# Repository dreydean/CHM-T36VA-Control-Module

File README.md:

View this project on [CADLAB.io](https://cadlab.io/project/2389). 

# CHM-T36VA-Control-Module
This is the control module to the CHM-T36VA pick and place machine. 

This is a work in progress. If anyone is able to contribute to this design please fork this repo! Hopefully this will give the OpenPNP community an opportunity to integrate into the CHM-T36VA. Feel free to contact me with any questions or suggestions!

You can eaily view this board or schematic on www.CADLAB.io

also you can view the Bill of Material here at this link.

BOM = https://octopart.com/bom-tool/2MmSibn2

As the project evolves I will make sure these stay up to date.

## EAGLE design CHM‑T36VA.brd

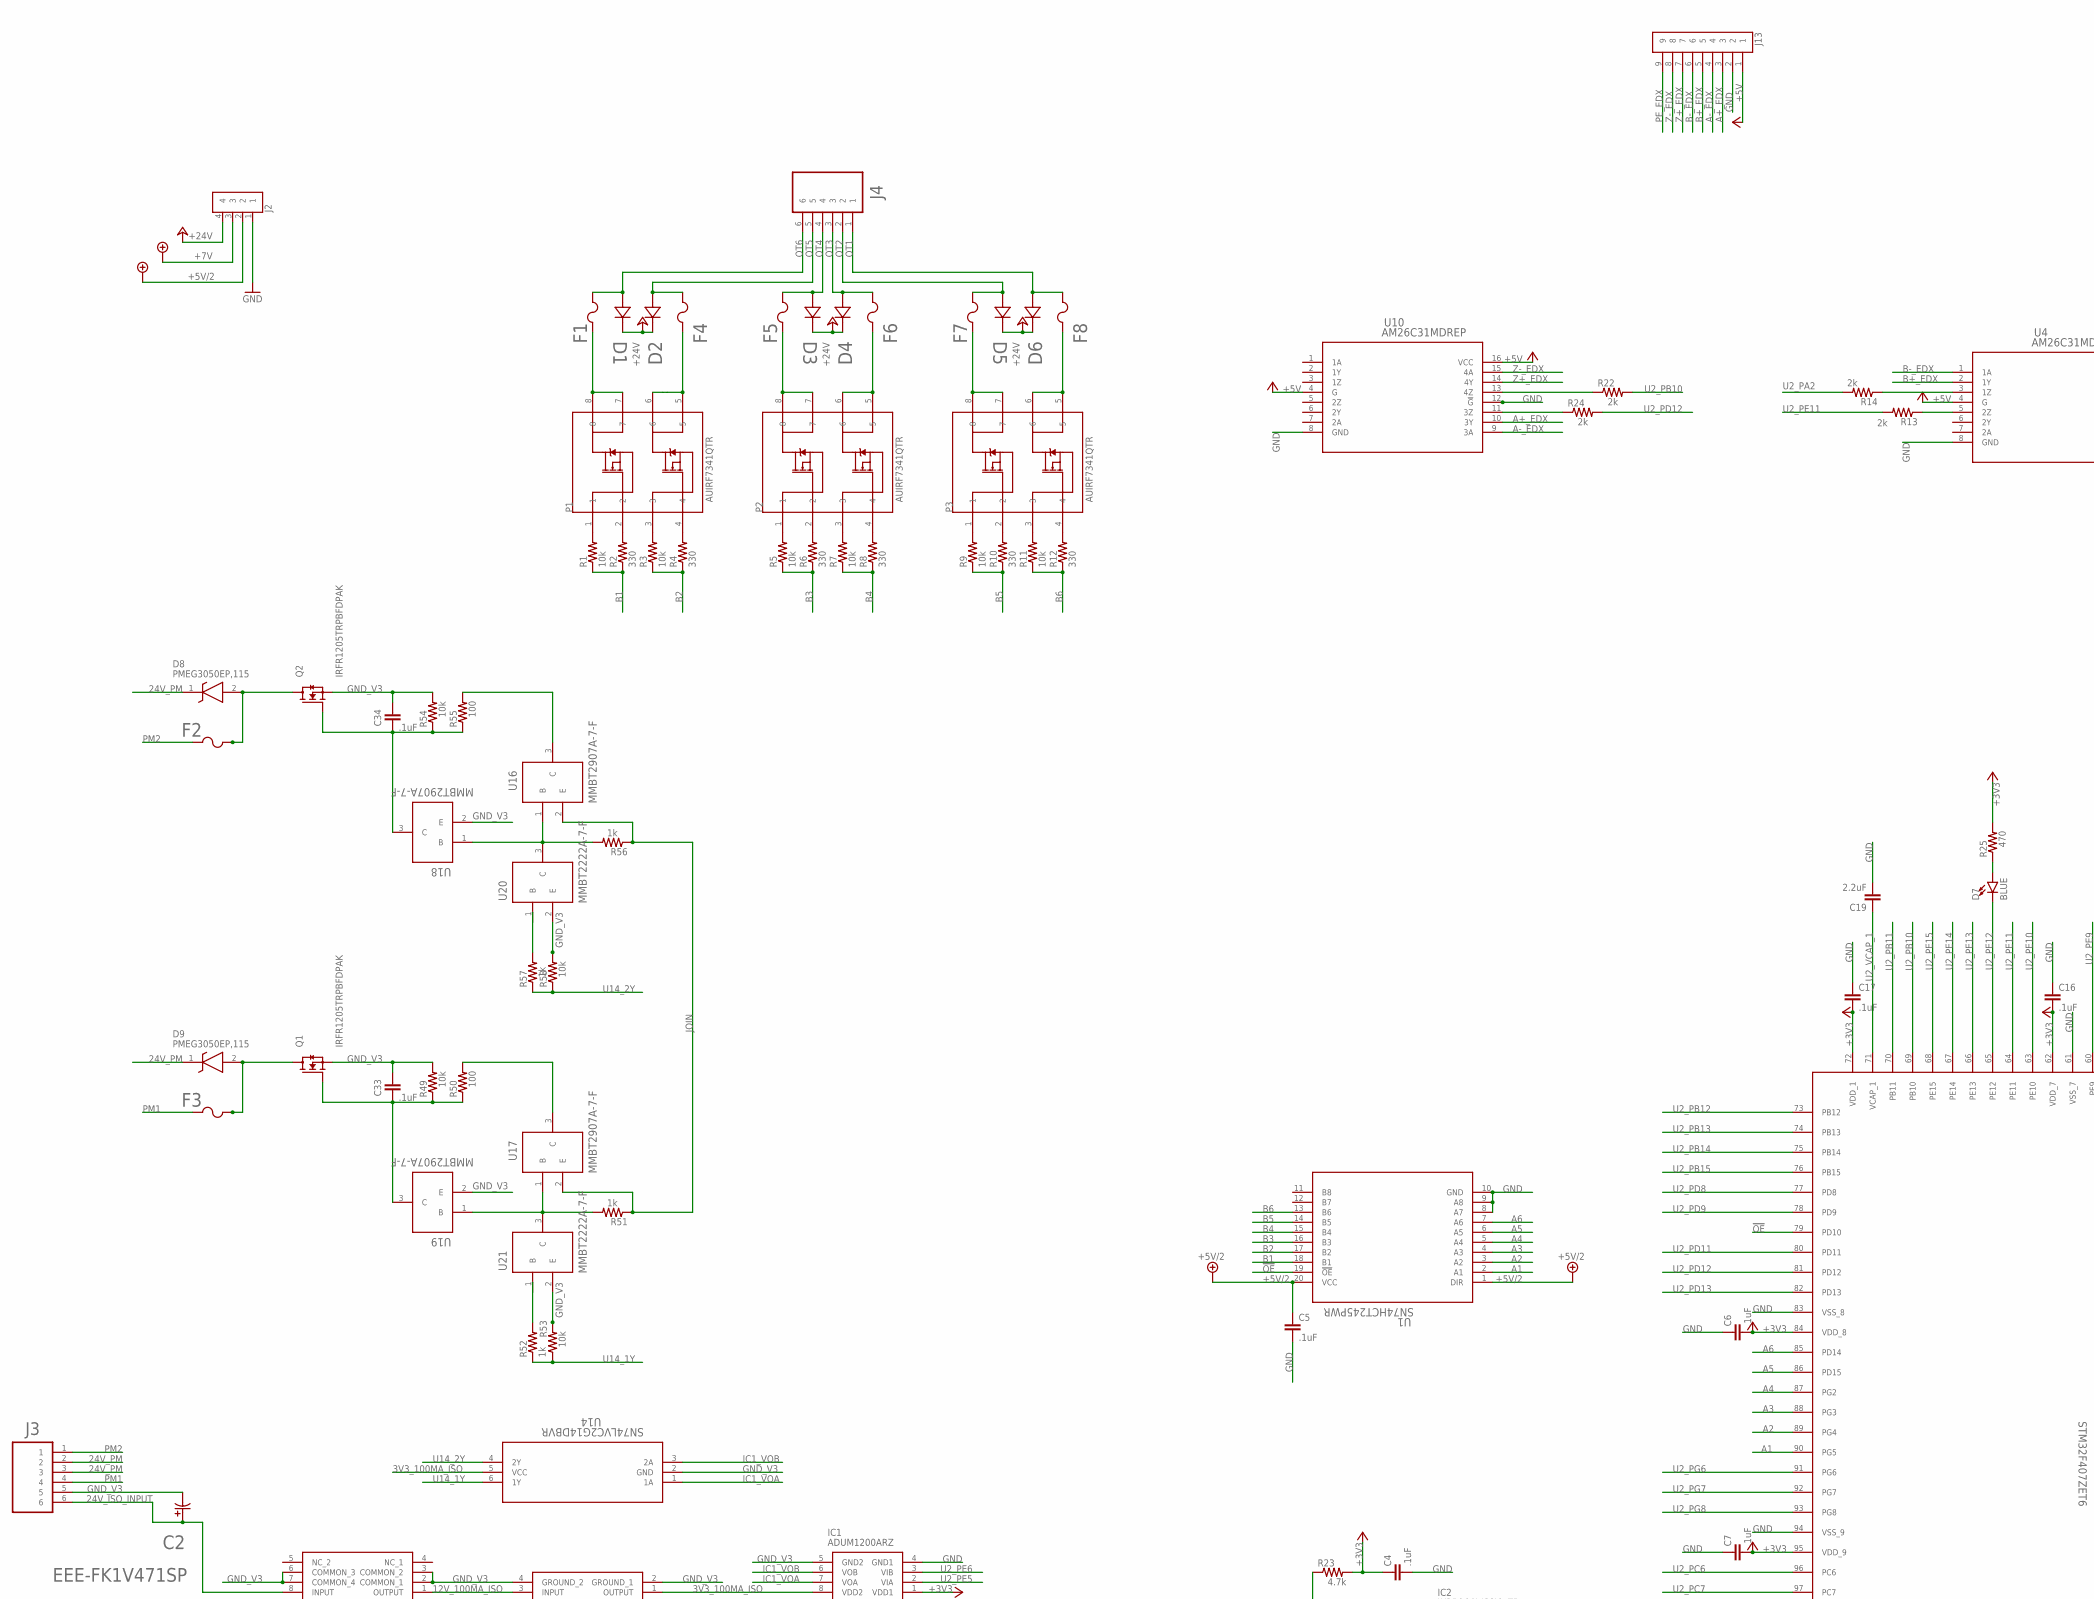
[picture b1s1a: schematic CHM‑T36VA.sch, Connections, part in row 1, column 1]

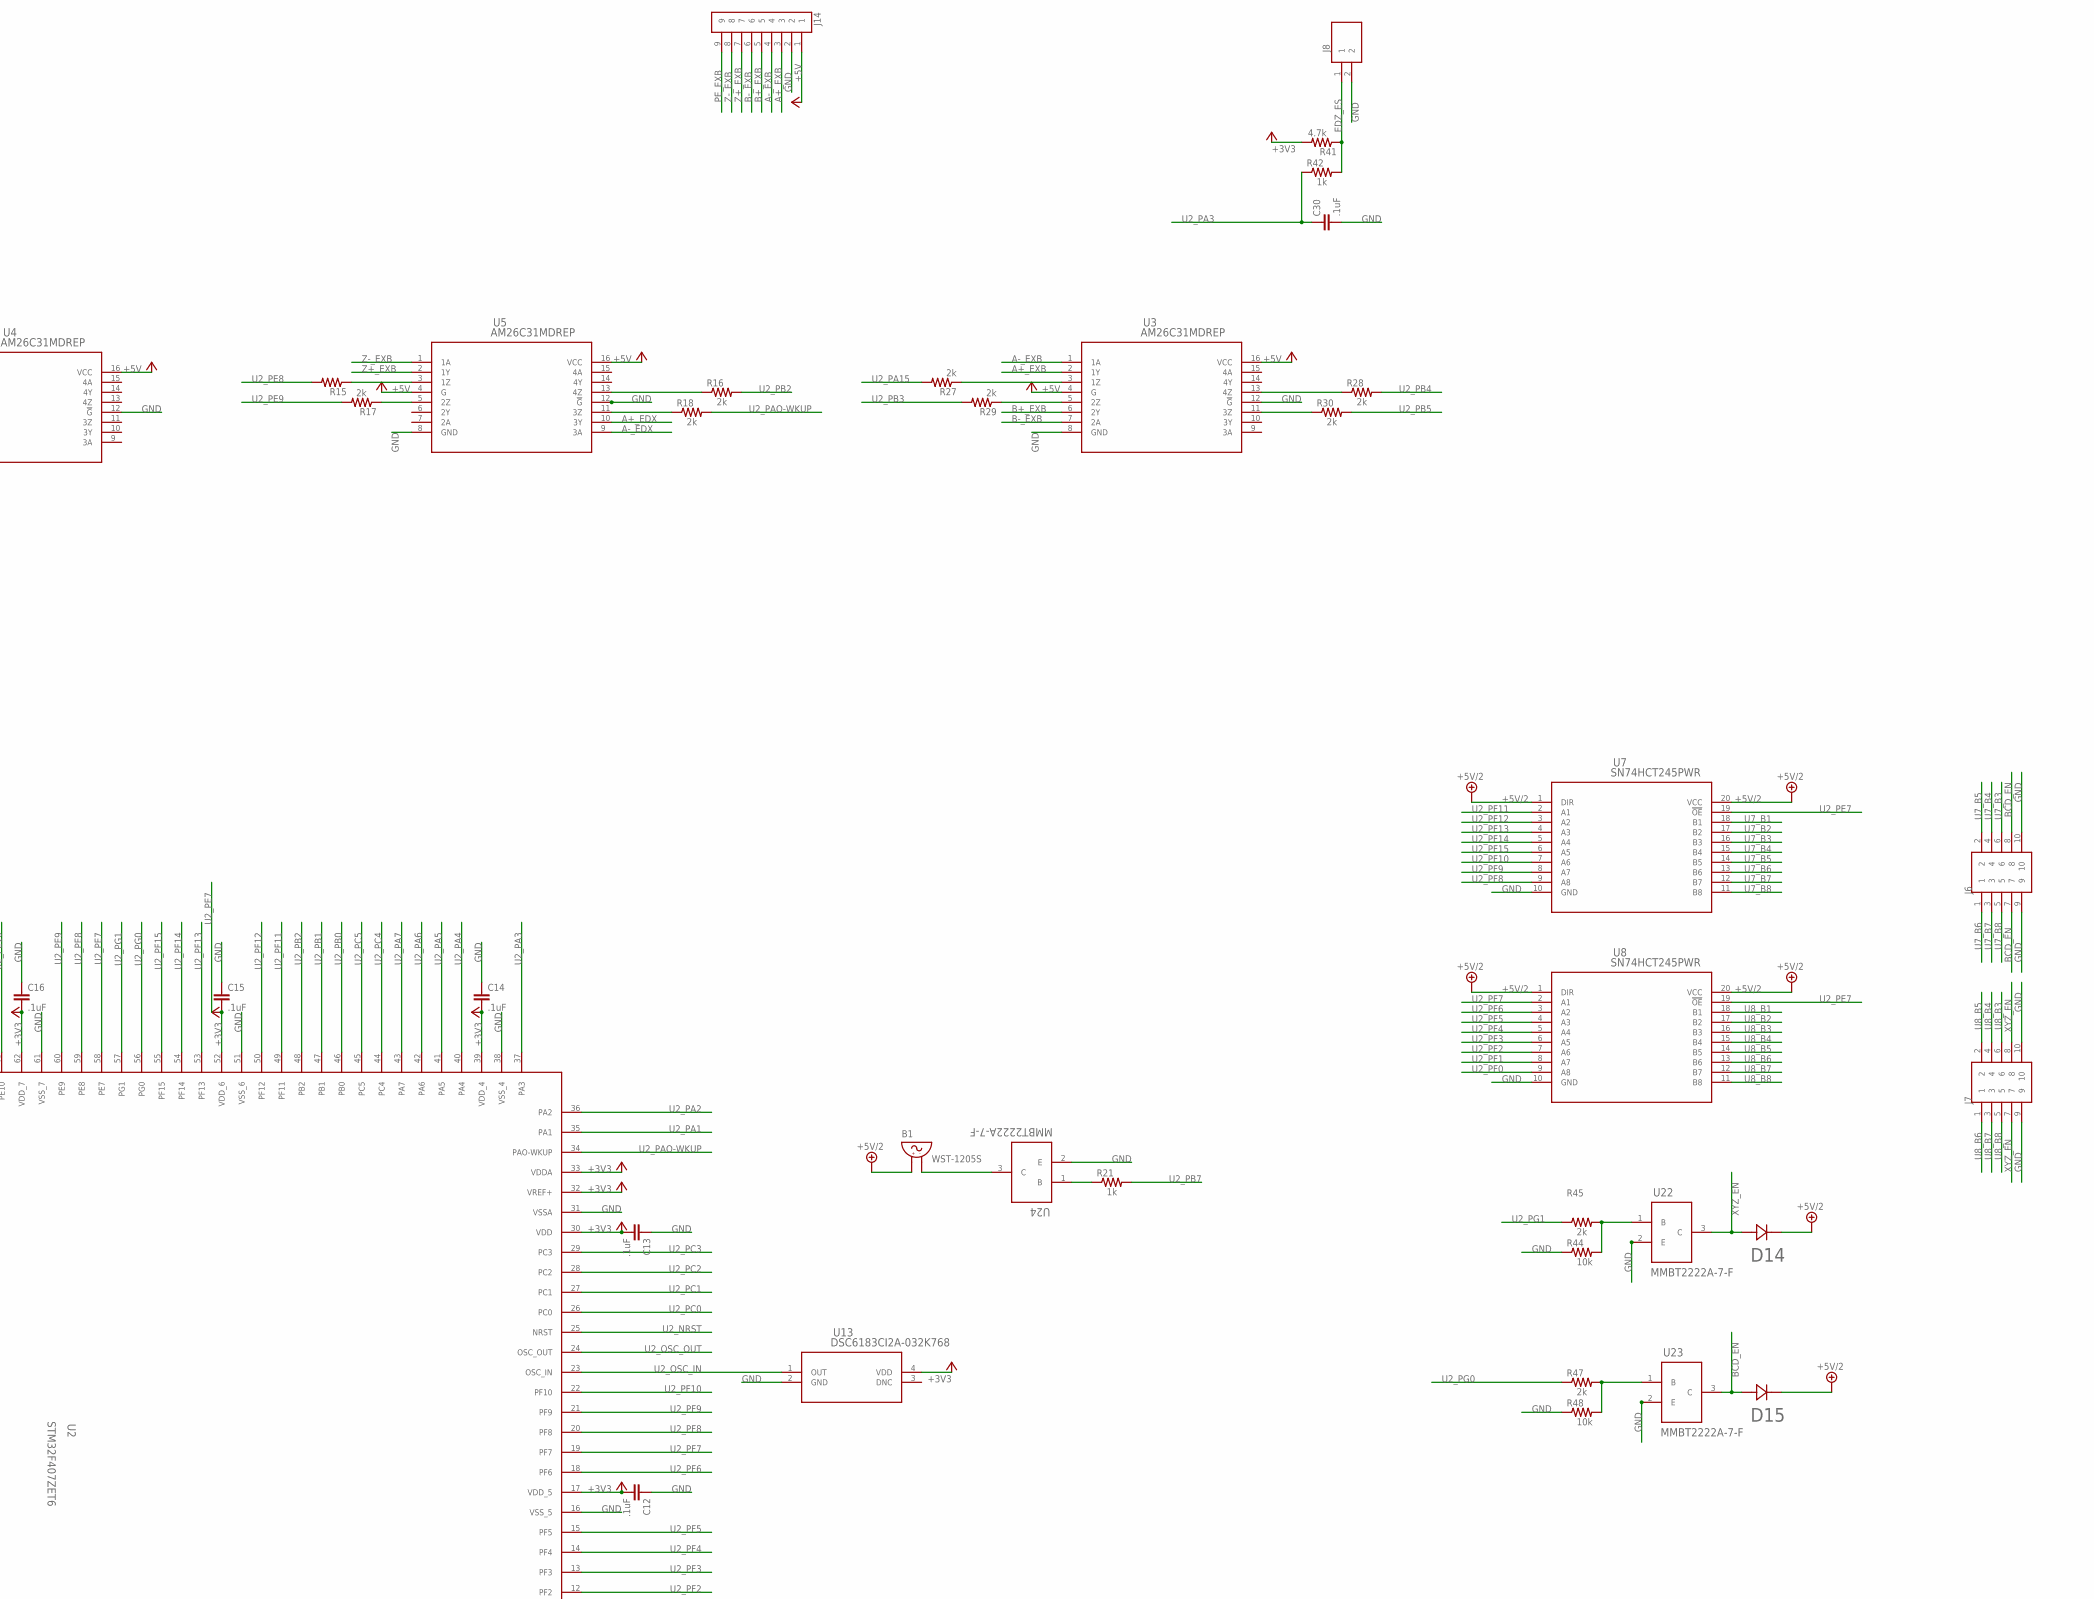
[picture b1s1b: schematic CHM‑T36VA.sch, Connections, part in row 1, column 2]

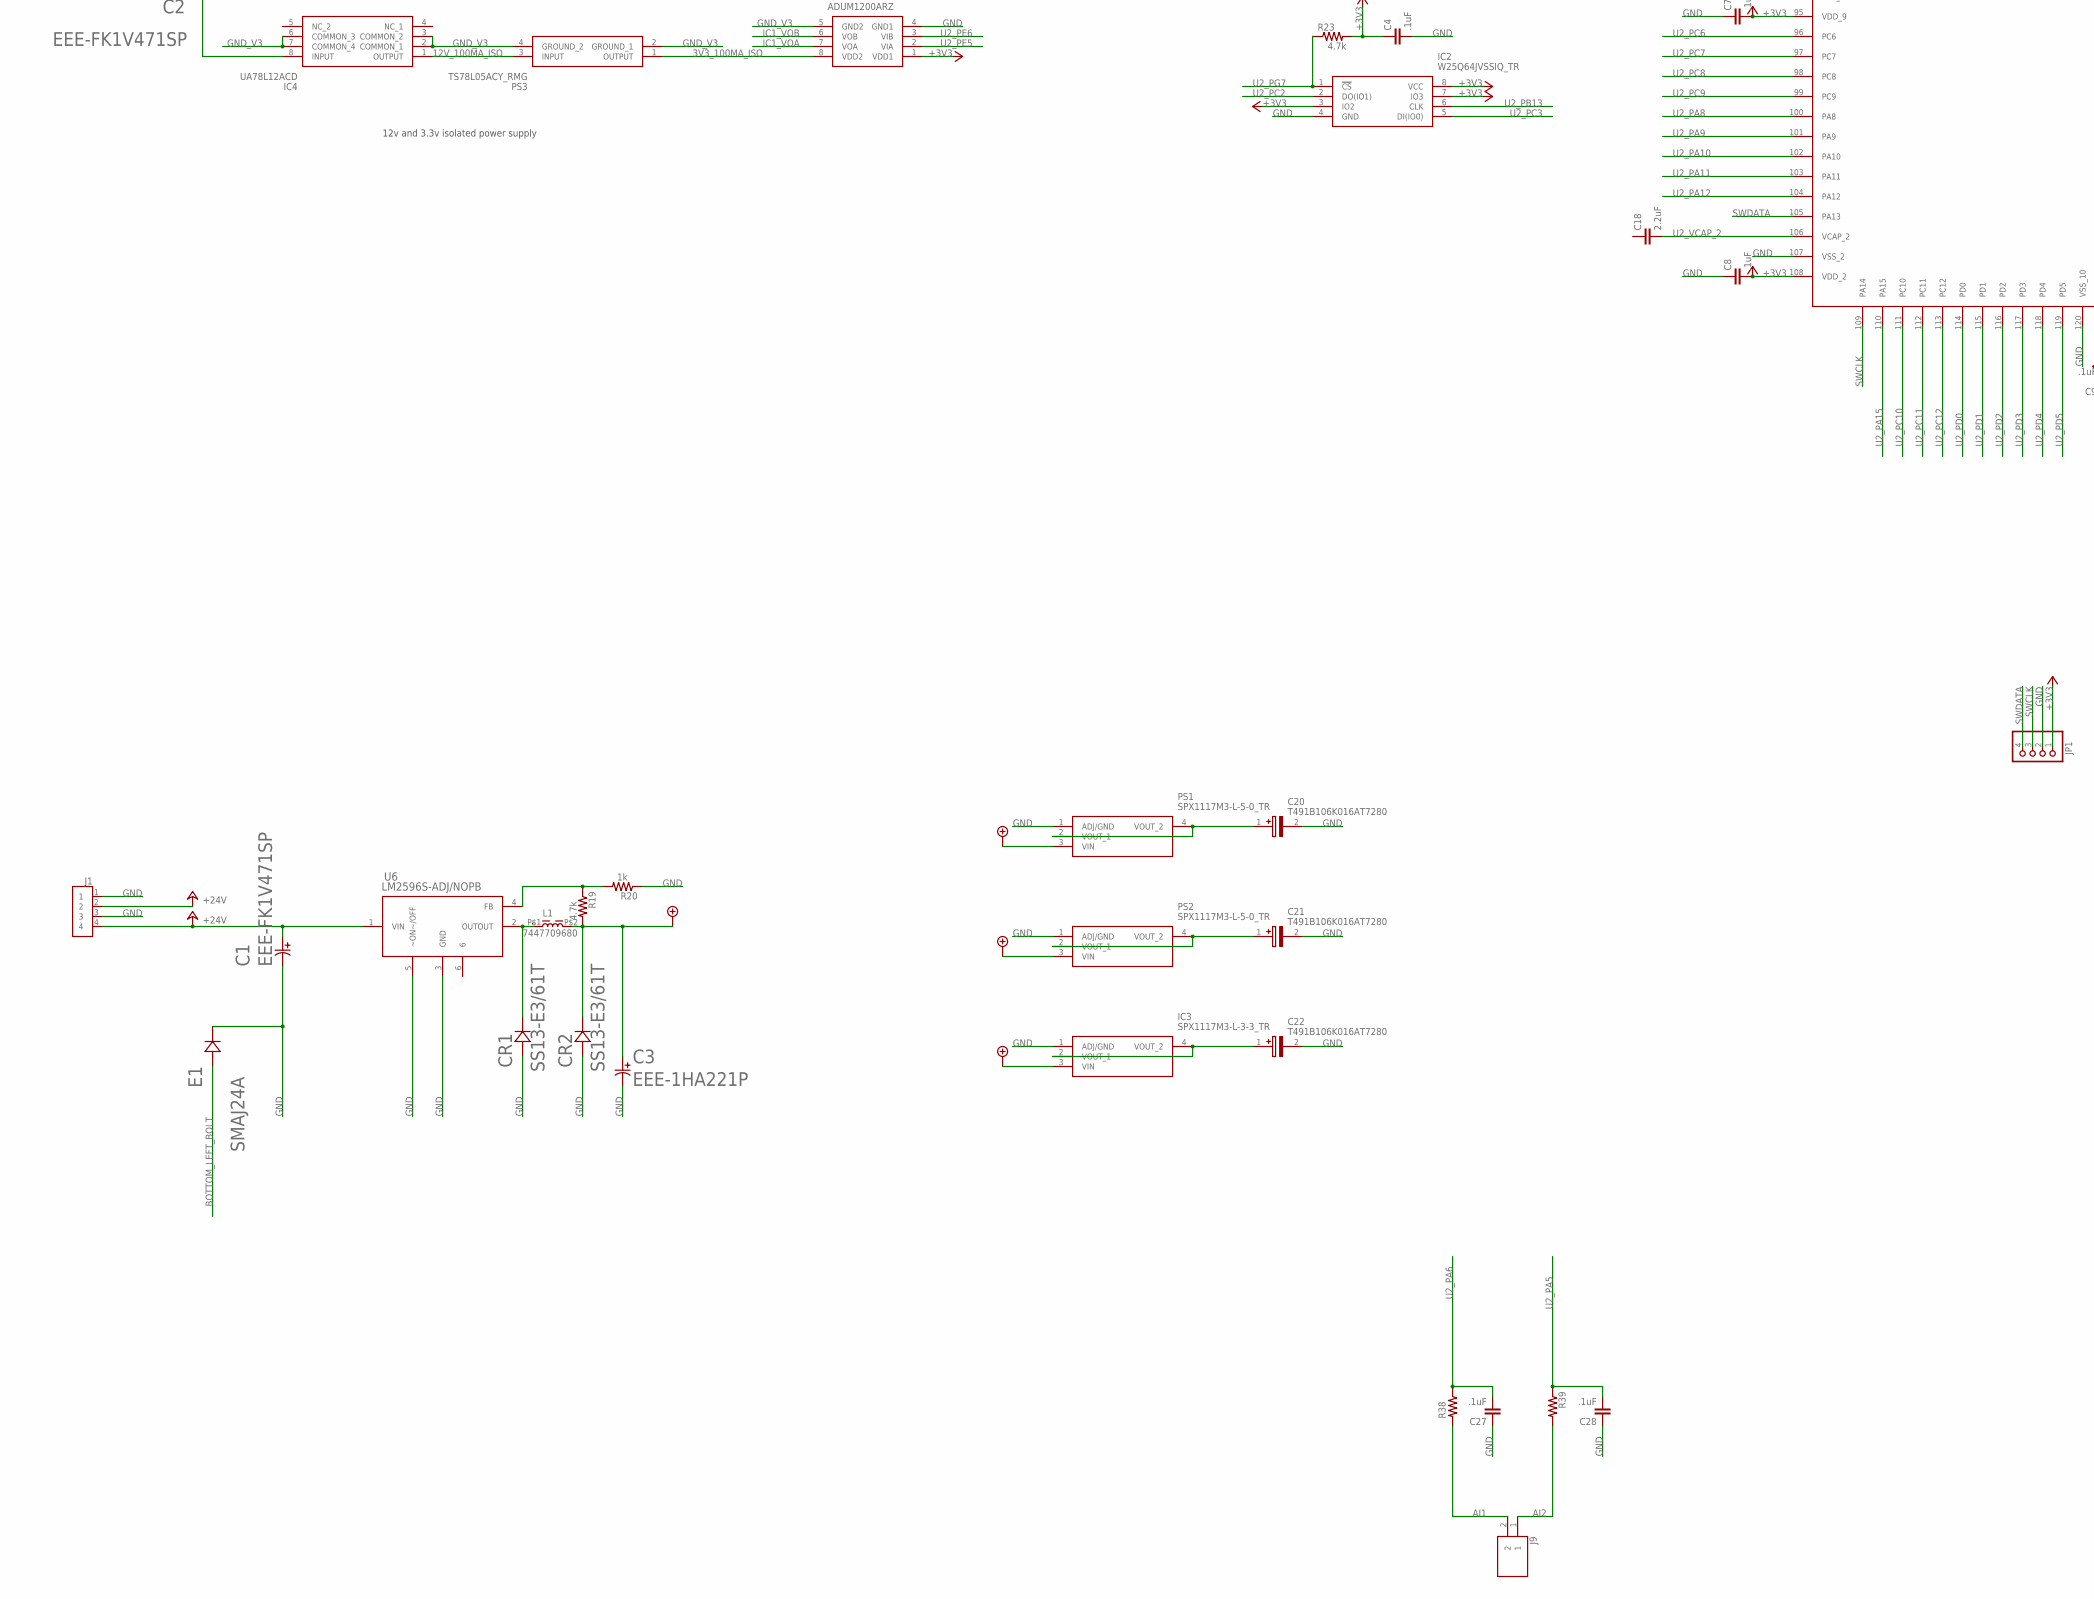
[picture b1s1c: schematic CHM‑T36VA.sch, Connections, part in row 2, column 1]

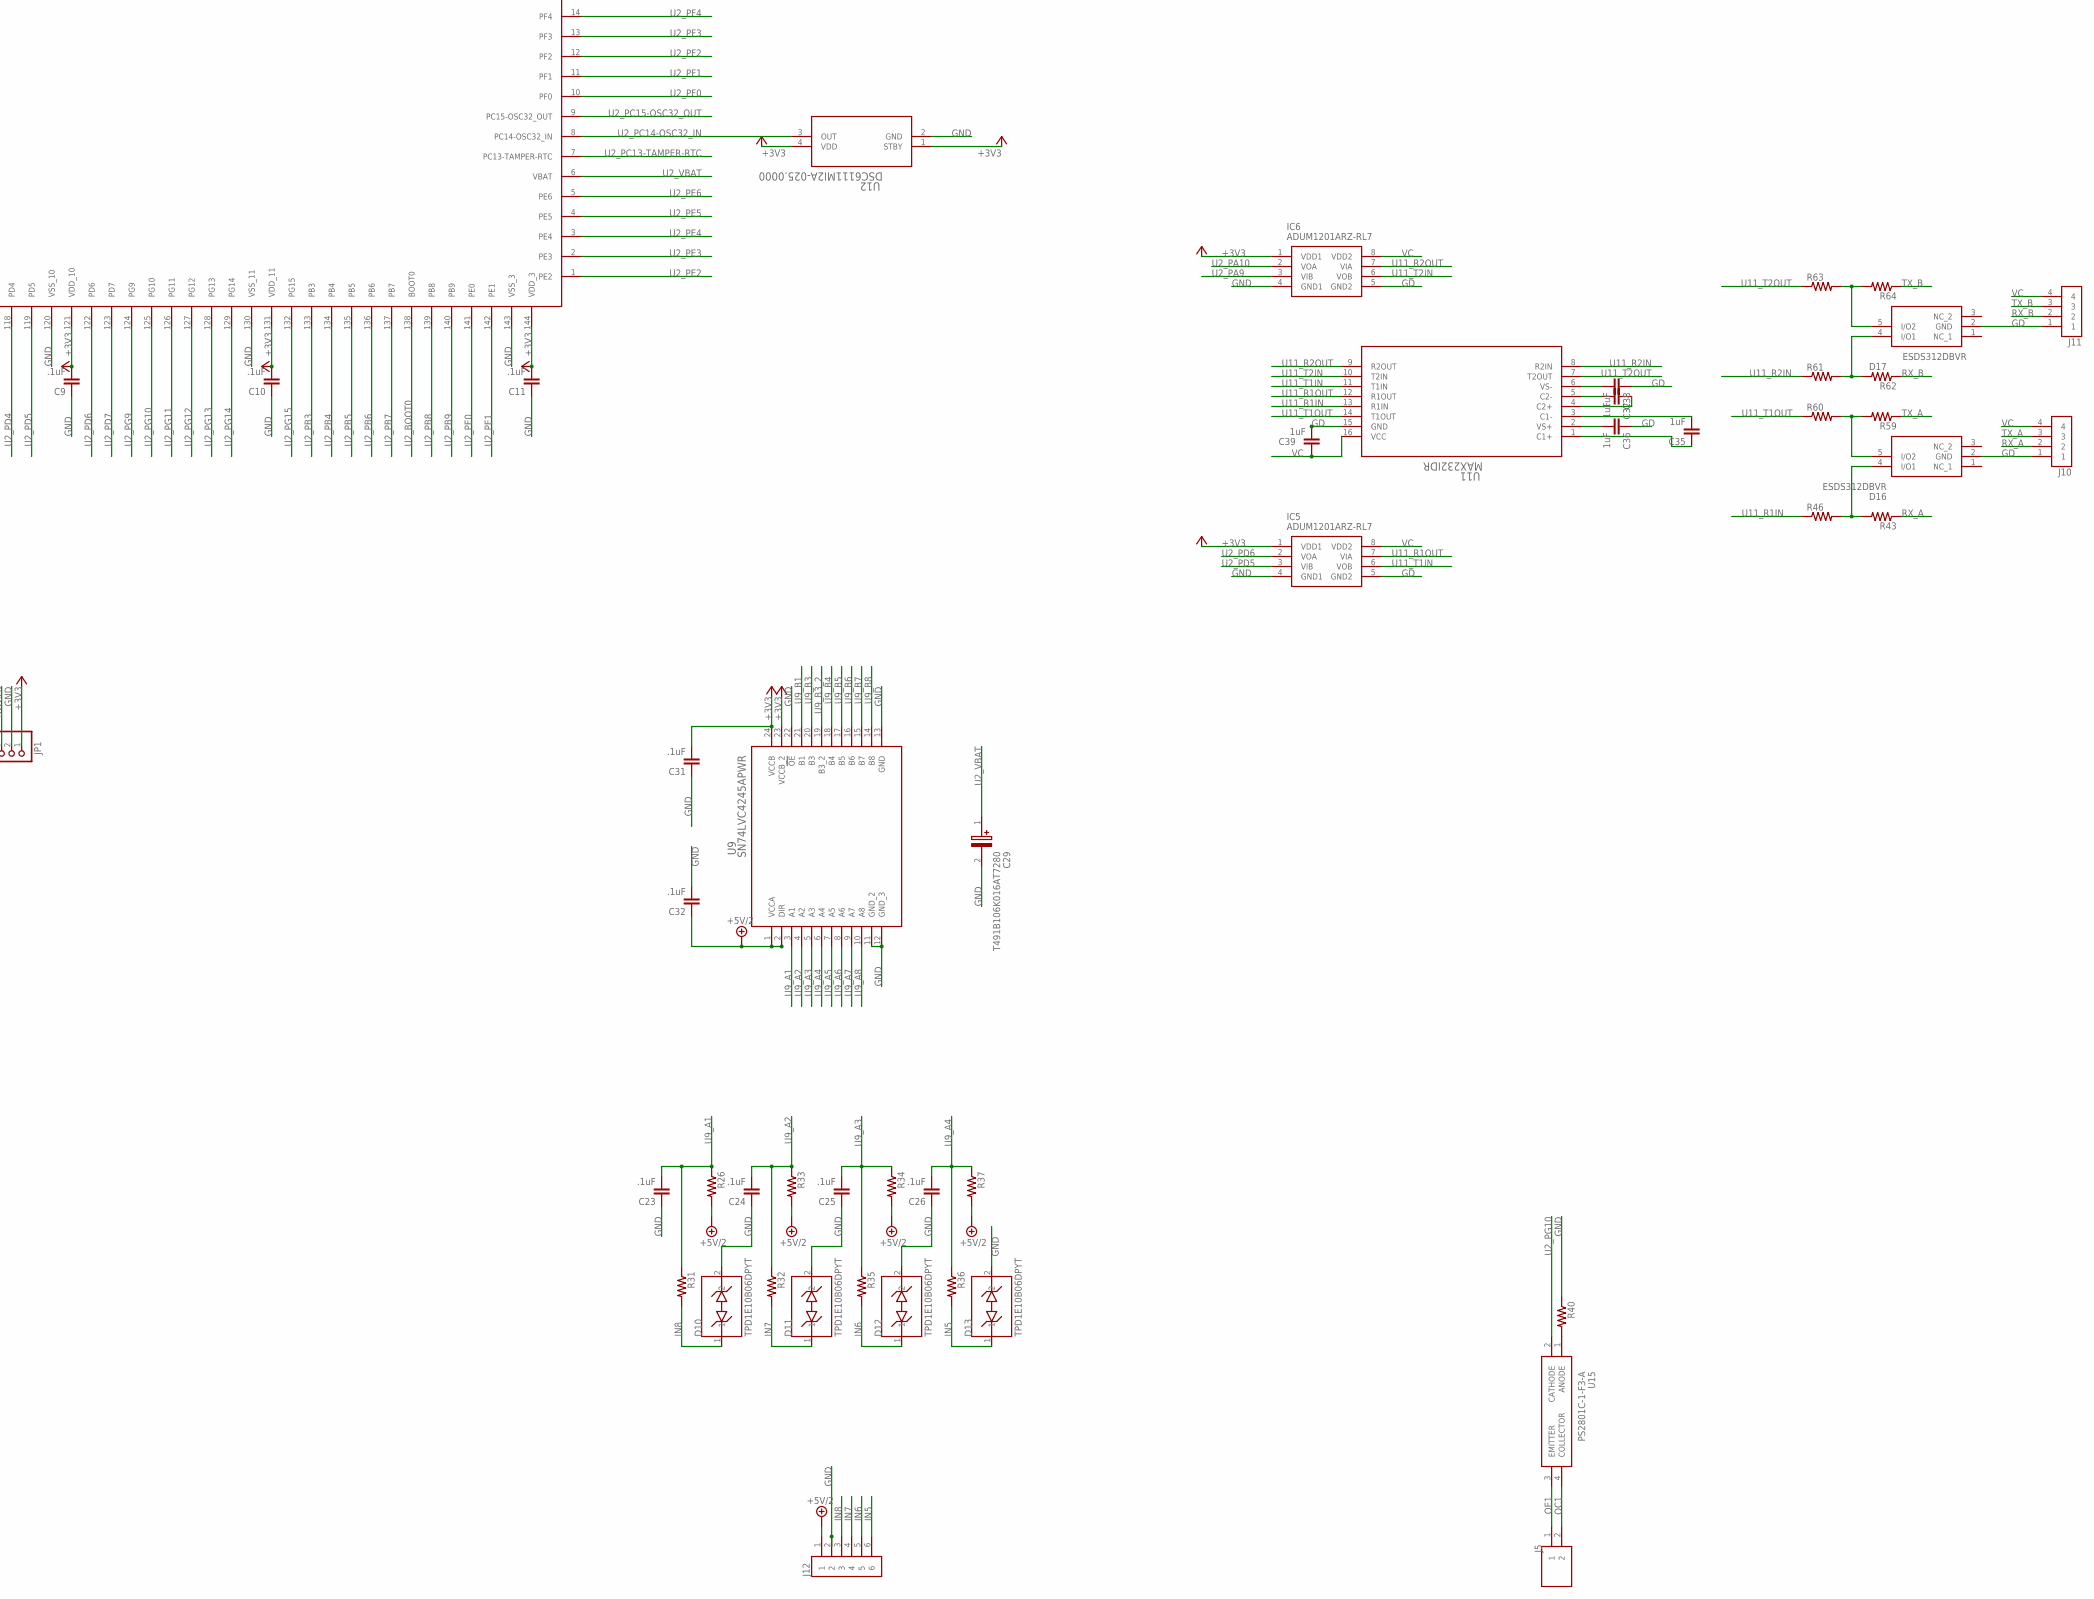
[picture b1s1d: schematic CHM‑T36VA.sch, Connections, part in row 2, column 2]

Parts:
B1: WST-1205S
C1, C2: EEE-FK1V471SP; FKS-V_G
C3: EEE-1HA221P; FKS-V_G
C4, C5, C6, C7, C8, C9, C10, C11, C12, C13, C14, C15, C16, C17, C23, C24, C25, C26, C27, C28, C30, C31, C32, C33, C34: .1uF; C0603
C18, C19: 2.2uF; C0603
C20, C21, C22, C29: T491B106K016AT7280; CAPPM3528X210N
C35, C36, C37, C38, C39: 1uF; C0603
CR1, CR2: SS13-E3/61T; DO-214AC
D1, D2, D3, D4, D5, D6, D14, D15: SS14-E3/61T; DO-214AC
D7: BLUE; LED-0603
D8, D9: PMEG3050EP,115; PMEG3050EP115
D10, D11, D12, D13: TPD1E10B06DPYT; DFN100X60X45-2N
D16, D17: ESDS312DBVR; SOT95P280X145-5N
E1: SMAJ24A; SMASERIES
F1, F2, F3, F4, F5, F6, F7, F8: RXEF110; FUS_RXEF110_TYCO
IC1: ADUM1200ARZ; SOIC127P600X175-8N
IC2: W25Q64JVSSIQ_TR; SOIC127P790X216-8N
IC3: SPX1117M3-L-3-3_TR; SOT230P700X180-4N
IC4: UA78L12ACD; SOIC127P600X175-8N
IC5, IC6: ADUM1201ARZ-RL7; SOIC127P600X175-8N
J1, J2: 1-1123723-4; TE_1-1123723-4
J3, J4: 1-1123723-6; TE_1-1123723-6
J5: 1546551-2; TE_1546551-2
J6, J7: 5499923-1; TE_5499923-1
J8, J9: B2B-XH-A(LF)(SN); JST_B2B-XH-A(LF)(SN)
J10, J11: B4B-XH-A(LF)(SN); JST_B4B-XH-A(LF)(SN)
J12: B6B-XH-A(LF)(SN); JST_B6B-XH-A(LF)(SN)
J13, J14: B9B-XH-A(LF)(SN); JST_B9B-XH-A(LF)(SN)
JP1: PINHD-1X4; 1X04
L1: 7447709680; 7447709101
P1, P2, P3: AUIRF7341QTR; SOIC127P600X168-9N
PS1, PS2: SPX1117M3-L-5-0_TR; SOT230P700X170-4N
PS3: TS78L05ACY_RMG; TS78L05ACYRMG
Q1, Q2: IRFR1205TRPBFDPAK; DPAK228P998X240-3N
R1, R3, R5, R7, R9, R11, R26, R33, R34, R37, R44, R48, R49, R53, R54, R58: 10k; R0603
R2, R4, R6, R8, R10, R12, R43, R46, R59, R60, R61, R62, R63, R64: 330; R0603
R13, R14, R15, R16, R17, R18, R22, R24, R27, R28, R29, R30, R45, R47: 2k; R0603
R19, R23, R41: 4.7k; R0603
R20, R21, R31, R32, R35, R36, R38, R39, R42, R51, R52, R56, R57: 1k; R0603
R25, R40: 470; R0603
R50, R55: 100; R0603
U1, U7, U8: SN74HCT245PWR; PW20
U2: STM32F407ZET6; LQFP-144
U3, U4, U5, U10: AM26C31MDREP; D16
U6: LM2596S-ADJ/NOPB; TS5B
U9: SN74LVC4245APWR; PW24
U11: MAX232IDR; D16
U12: DSC6111MI2A-025.0000; VFLGA4_2X1.6
U13: DSC6183CI2A-032K768; DFN4_3.2X2.5
U14: SN74LVC2G14DBVR; DBV6
U15: PS2801C-1-F3-A; SOIC127P700X210-4N
U16, U17, U18, U19: MMBT2907A-7-F; SOT-23
U20, U21, U22, U23, U24: MMBT2222A-7-F; SOT-23

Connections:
3V3_100MA_ISO: IC1.8 (VDD2), PS3.1 (OUTPUT), U14.5 (VCC)
12V_100MA_ISO: IC4.1 (OUTPUT), PS3.3 (INPUT)
24V_ISO_INPUT: C2.2, IC4.8 (INPUT), J3.6
24V_PM: D8.1 (K), D9.1 (K), J3.2, J3.3
!OE: U1.19 (!OE), U2.79 (PD10)
+3V3: C4.1, C6.2, C7.2, C8.2, C9.2, C10.2, C11.2, C12.2, C13.2, C14.2, C15.2, C16.2, C17.2, C31.2, IC1.1 (VDD1), IC2.3 (IO2), IC2.7 (IO3), IC2.8 (VCC), IC5.1 (VDD1), IC6.1 (VDD1), JP1.1, R23.2, R25.2, R41.2, U2.17 (VDD_5), U2.30 (VDD), U2.32 (VREF+), U2.33 (VDDA), U2.39 (VDD_4), U2.52 (VDD_6), U2.62 (VDD_7), U2.72 (VDD_1), U2.84 (VDD_8), U2.95 (VDD_9), U2.108 (VDD_2), U2.121 (VDD_10), U2.131 (VDD_11), U2.144 (VDD_3), U9.23 (VCCB_2), U9.24 (VCCB), U12.1 (STBY), U12.4 (VDD), U13.4 (VDD)
+5V: J13.1, J14.1, U3.4 (G), U3.16 (VCC), U4.4 (G), U4.16 (VCC), U5.4 (G), U5.16 (VCC), U10.4 (G), U10.16 (VCC)
+5V/2: B1.+ (1), C5.1, C32.1, D14.1, D15.1, J2.2, J12.1, R26.2, R33.2, R34.2, R37.2, U1.1 (DIR), U1.20 (VCC), U7.1 (DIR), U7.20 (VCC), U8.1 (DIR), U8.20 (VCC), U9.1 (VCCA), U9.2 (DIR)
+7V: C3.2, CR2.1, IC3.3 (VIN), J2.3, L1.P$2 (2), PS1.3 (VIN), PS2.3 (VIN), R19.2
+24V: C1.2, D1.1, D2.1, D3.1, D4.1, D5.1, D6.1, J1.2, J1.4, J2.4, U6.1 (VIN)
A1: U1.2 (A1), U2.90 (PG5)
A2: U1.3 (A2), U2.89 (PG4)
A3: U1.4 (A3), U2.88 (PG3)
A4: U1.5 (A4), U2.87 (PG2)
A5: U1.6 (A5), U2.86 (PD15)
A6: U1.7 (A6), U2.85 (PD14)
A+_EDX: J13.3, U5.10 (3Y), U10.10 (3Y)
A+_EXB: J14.3, U3.2 (1Y)
A-_EDX: J13.4, U5.9 (3A), U10.9 (3A)
A-_EXB: J14.4, U3.1 (1A)
AI1: J9.2, R38.2
AI2: J9.1, R39.2
B1: R1.1, R2.1, U1.18 (B1)
B2: R3.1, R4.1, U1.17 (B2)
B3: R5.1, R6.1, U1.16 (B3)
B4: R7.1, R8.1, U1.15 (B4)
B5: R9.1, R10.1, U1.14 (B5)
B6: R11.1, R12.1, U1.13 (B6)
B+_EDX: J13.5, U4.2 (1Y)
B+_EXB: J14.5, U3.6 (2Y)
B-_EDX: J13.6, U4.1 (1A)
B-_EXB: J14.6, U3.7 (2A)
BCD_EN: D15.2, J6.7, J6.8, U23.3 (C)
BOTTOM_LEFT_BOLT: E1.2
EDZ_ES: J8.1, R41.1, R42.2
GD: C36.1, C38.1, C39.2, D16.2 (GND), D17.2 (GND), IC5.5 (GND2), IC6.5 (GND2), J10.1, J11.1, U11.15 (GND)
GND: C1.1, C3.1, C4.2, C5.2, C6.1, C7.1, C8.1, C9.1, C10.1, C11.1, C12.1, C13.1, C14.1, C15.1, C16.1, C17.1, C19.2, C20.2 (-), C21.2 (-), C22.2 (-), C23.1, C24.1, C25.1, C26.1, C27.1, C28.1, C29.2 (-), C30.2, C31.1, C32.2, CR1.2, CR2.2, D10.2, D11.2, D12.2, D13.2, E1.1, IC1.4 (GND1), IC2.4 (GND), IC3.1 (ADJ/GND), IC5.4 (GND1), IC6.4 (GND1), J1.1, J1.3, J2.1, J6.9, J6.10, J7.9, J7.10, J8.2, J12.2, J13.2, J14.2, JP1.2, PS1.1 (ADJ/GND), PS2.1 (ADJ/GND), R20.1, R40.1, R44.1, R48.1, U1.8 (A7), U1.9 (A8), U1.10 (GND), U2.16 (VSS_5), U2.31 (VSSA), U2.38 (VSS_4), U2.51 (VSS_6), U2.61 (VSS_7), U2.83 (VSS_8), U2.94 (VSS_9), U2.107 (VSS_2), U2.120 (VSS_10), U2.130 (VSS_11), U2.143 (VSS_3), U3.8 (GND), U3.12 (!G), U4.8 (GND), U4.12 (!G), U5.8 (GND), U5.12 (!G), U6.3 (GND), U6.5 (~ON~/OFF), U7.10 (GND), U8.10 (GND), U9.11 (GND_2), U9.12 (GND_3), U9.13 (GND), U9.22 (!OE), U10.8 (GND), U10.12 (!G), U12.2 (GND), U13.2 (GND), U22.2 (E), U23.2 (E), U24.2 (E)
GND_V3: C2.1, C33.1, C34.1, IC1.5 (GND2), IC4.2 (COMMON_1), IC4.3 (COMMON_2), IC4.6 (COMMON_3), IC4.7 (COMMON_4), J3.5, PS3.2 (GROUND_1), PS3.4 (GROUND_2), Q1.3 (S), Q2.3 (S), R49.2, R53.2, R54.2, R58.2, U14.2 (GND), U18.2 (E), U19.2 (E), U20.2 (E), U21.2 (E)
IC1_VOA: IC1.7 (VOA), U14.1 (1A)
IC1_VOB: IC1.6 (VOB), U14.3 (2A)
IN5: D13.1, J12.6, R36.2
IN6: D12.1, J12.5, R35.2
IN7: D11.1, J12.4, R32.2
IN8: D10.1, J12.3, R31.2
JOIN: R51.1, R56.1, U16.2 (E), U17.2 (E)
unnamed: F4.1, P1.5, P1.6
unnamed: P1.1, R1.2
unnamed: P1.2, R2.2
unnamed: F1.1, P1.7, P1.8
unnamed: F6.1, P2.5, P2.6
unnamed: F5.1, P2.7, P2.8
unnamed: R16.1, U5.13 (4Z)
unnamed: F7.1, P3.7, P3.8
unnamed: F8.1, P3.5, P3.6
unnamed: P1.3, R3.2
unnamed: P1.4, R4.2
unnamed: P2.1, R5.2
unnamed: P2.2, R6.2
unnamed: P2.3, R7.2
unnamed: P2.4, R8.2
unnamed: R15.1, U5.3 (1Z)
unnamed: P3.1, R9.2
unnamed: P3.2, R10.2
unnamed: P3.3, R11.2
unnamed: P3.4, R12.2
unnamed: R17.1, U5.5 (2Z)
unnamed: R18.1, U5.11 (3Z)
unnamed: R27.1, U3.3 (1Z)
unnamed: R28.1, U3.13 (4Z)
unnamed: R29.1, U3.5 (2Z)
unnamed: R30.1, U3.11 (3Z)
unnamed: R13.1, U4.5 (2Z)
unnamed: R14.1, U4.3 (1Z)
unnamed: R19.1, R20.2, U6.4 (FB)
unnamed: D16.4 (I/O1), R43.2, R46.2
unnamed: D16.5 (I/O2), R59.2, R60.2
unnamed: CR1.1, L1.P$1 (1), U6.2 (OUTOUT)
unnamed: R21.1, U24.1 (B)
unnamed: R22.1, U10.13 (4Z)
unnamed: B1.- (2), U24.3 (C)
unnamed: R24.1, U10.11 (3Z)
unnamed: D7.A, R25.1
unnamed: C20.1 (+), PS1.2 (VOUT_1), PS1.4 (VOUT_2)
unnamed: C21.1 (+), PS2.2 (VOUT_1), PS2.4 (VOUT_2)
unnamed: C22.1 (+), IC3.2 (VOUT_1), IC3.4 (VOUT_2)
unnamed: D9.2 (A), F3.2, Q1.2 (D)
unnamed: D8.2 (A), F2.2, Q2.2 (D)
unnamed: R40.2, U15.1 (ANODE)
unnamed: D17.4 (I/O1), R61.2, R62.2
unnamed: R51.2, U17.1 (B), U19.1 (B), U21.3 (C)
unnamed: R44.2, R45.2, U22.1 (B)
unnamed: R56.2, U16.1 (B), U18.1 (B), U20.3 (C)
unnamed: R47.2, R48.2, U23.1 (B)
unnamed: R52.2, U21.1 (B)
unnamed: C33.2, Q1.1 (G), R49.1, R50.1, U19.3 (C)
unnamed: R50.2, U17.3 (C)
unnamed: R57.2, U20.1 (B)
unnamed: C34.2, Q2.1 (G), R54.1, R55.1, U18.3 (C)
unnamed: R55.2, U16.3 (C)
unnamed: D17.5 (I/O2), R63.2, R64.2
unnamed: C36.2, U11.2 (VS+)
unnamed: C35.2, U11.3 (C1-)
unnamed: C37.2, U11.5 (C2-)
unnamed: C37.1, U11.4 (C2+)
unnamed: C38.2, U11.6 (VS-)
unnamed: C35.1, U11.1 (C1+)
OC1: J5.2, U15.4 (COLLECTOR)
OE1: J5.1, U15.3 (EMITTER)
OT1: D6.2, F8.2, J4.1
OT2: D5.2, F7.2, J4.2
OT3: D4.2, F6.2, J4.3
OT4: D3.2, F5.2, J4.4
OT5: D2.2, F4.2, J4.5
OT6: D1.2, F1.2, J4.6
PE_EDX: J13.9
PE_EXB: J14.9
PM1: F3.1, J3.4
PM2: F2.1, J3.1
RX_A: J10.2, R43.1
RX_B: J11.2, R62.1
SWCLK: JP1.3, U2.109 (PA14)
SWDATA: JP1.4, U2.105 (PA13)
TX_A: J10.3, R59.1
TX_B: J11.3, R64.1
U2_BOOT0: U2.138 (BOOT0)
U2_NRST: U2.25 (NRST)
U2_OSC_IN: U2.23 (OSC_IN), U13.1 (OUT)
U2_OSC_OUT: U2.24 (OSC_OUT)
U2_PA1: U2.35 (PA1)
U2_PA2: R14.2, U2.36 (PA2)
U2_PA3: C30.1, R42.1, U2.37 (PA3)
U2_PA4: U2.40 (PA4)
U2_PA5: C28.2, R39.1, U2.41 (PA5)
U2_PA6: C27.2, R38.1, U2.42 (PA6)
U2_PA7: U2.43 (PA7)
U2_PA8: U2.100 (PA8)
U2_PA9: IC6.3 (VIB), U2.101 (PA9)
U2_PA10: IC6.2 (VOA), U2.102 (PA10)
U2_PA11: U2.103 (PA11)
U2_PA12: U2.104 (PA12)
U2_PA15: R27.2, U2.110 (PA15)
U2_PAO-WKUP: R18.2, U2.34 (PAO-WKUP)
U2_PB0: U2.46 (PB0)
U2_PB1: U2.47 (PB1)
U2_PB2: R16.2, U2.48 (PB2)
U2_PB3: R29.2, U2.133 (PB3)
U2_PB4: R28.2, U2.134 (PB4)
U2_PB5: R30.2, U2.135 (PB5)
U2_PB6: U2.136 (PB6)
U2_PB7: R21.2, U2.137 (PB7)
U2_PB8: U2.139 (PB8)
U2_PB9: U2.140 (PB9)
U2_PB10: R22.2, U2.69 (PB10)
U2_PB11: U2.70 (PB11)
U2_PB12: U2.73 (PB12)
U2_PB13: IC2.6 (CLK), U2.74 (PB13)
U2_PB14: U2.75 (PB14)
U2_PB15: U2.76 (PB15)
U2_PC0: U2.26 (PC0)
U2_PC1: U2.27 (PC1)
U2_PC2: IC2.2 (DO(IO1)), U2.28 (PC2)
U2_PC3: IC2.5 (DI(IO0)), U2.29 (PC3)
U2_PC4: U2.44 (PC4)
U2_PC5: U2.45 (PC5)
U2_PC6: U2.96 (PC6)
U2_PC7: U2.97 (PC7)
U2_PC8: U2.98 (PC8)
U2_PC9: U2.99 (PC9)
U2_PC10: U2.111 (PC10)
U2_PC11: U2.112 (PC11)
U2_PC12: U2.113 (PC12)
U2_PC13-TAMPER-RTC: U2.7 (PC13-TAMPER-RTC)
U2_PC14-OSC32_IN: U2.8 (PC14-OSC32_IN), U12.3 (OUT)
U2_PC15-OSC32_OUT: U2.9 (PC15-OSC32_OUT)
U2_PD0: U2.114 (PD0)
U2_PD1: U2.115 (PD1)
U2_PD2: U2.116 (PD2)
U2_PD3: U2.117 (PD3)
U2_PD4: U2.118 (PD4)
U2_PD5: IC5.3 (VIB), U2.119 (PD5)
U2_PD6: IC5.2 (VOA), U2.122 (PD6)
U2_PD7: U2.123 (PD7)
U2_PD8: U2.77 (PD8)
U2_PD9: U2.78 (PD9)
U2_PD11: U2.80 (PD11)
U2_PD12: R24.2, U2.81 (PD12)
U2_PD13: U2.82 (PD13)
U2_PE0: U2.141 (PE0)
U2_PE1: U2.142 (PE1)
U2_PE2: U2.1 (PE2)
U2_PE3: U2.2 (PE3)
U2_PE4: U2.3 (PE4)
U2_PE5: IC1.2 (VIA), U2.4 (PE5)
U2_PE6: IC1.3 (VIB), U2.5 (PE6)
U2_PE7: U2.58 (PE7), U7.19 (!OE), U8.19 (!OE)
U2_PE8: R15.2, U2.59 (PE8)
U2_PE9: R17.2, U2.60 (PE9)
U2_PE10: U2.63 (PE10)
U2_PE11: R13.2, U2.64 (PE11)
U2_PE12: D7.C, U2.65 (PE12)
U2_PE13: U2.66 (PE13)
U2_PE14: U2.67 (PE14)
U2_PE15: U2.68 (PE15)
U2_PF0: U2.10 (PF0), U8.9 (A8)
U2_PF1: U2.11 (PF1), U8.8 (A7)
U2_PF2: U2.12 (PF2), U8.7 (A6)
U2_PF3: U2.13 (PF3), U8.6 (A5)
U2_PF4: U2.14 (PF4), U8.5 (A4)
U2_PF5: U2.15 (PF5), U8.4 (A3)
U2_PF6: U2.18 (PF6), U8.3 (A2)
U2_PF7: U2.19 (PF7), U8.2 (A1)
U2_PF8: U2.20 (PF8), U7.9 (A8)
U2_PF9: U2.21 (PF9), U7.8 (A7)
U2_PF10: U2.22 (PF10), U7.7 (A6)
U2_PF11: U2.49 (PF11), U7.2 (A1)
U2_PF12: U2.50 (PF12), U7.3 (A2)
U2_PF13: U2.53 (PF13), U7.4 (A3)
U2_PF14: U2.54 (PF14), U7.5 (A4)
U2_PF15: U2.55 (PF15), U7.6 (A5)
U2_PG0: R47.1, U2.56 (PG0)
U2_PG1: R45.1, U2.57 (PG1)
U2_PG6: U2.91 (PG6)
U2_PG7: IC2.1 (!CS), R23.1, U2.92 (PG7)
U2_PG8: U2.93 (PG8)
U2_PG9: U2.124 (PG9)
U2_PG10: U2.125 (PG10), U15.2 (CATHODE)
U2_PG11: U2.126 (PG11)
U2_PG12: U2.127 (PG12)
U2_PG13: U2.128 (PG13)
U2_PG14: U2.129 (PG14)
U2_PG15: U2.132 (PG15)
U2_VBAT: C29.1 (+), U2.6 (VBAT)
U2_VCAP_1: C19.1, U2.71 (VCAP_1)
U2_VCAP_2: C18.2, U2.106 (VCAP_2)
U7_B1: U7.18 (B1)
U7_B2: U7.17 (B2)
U7_B3: J6.6, U7.16 (B3)
U7_B4: J6.4, U7.15 (B4)
U7_B5: J6.2, U7.14 (B5)
U7_B6: J6.1, U7.13 (B6)
U7_B7: J6.3, U7.12 (B7)
U7_B8: J6.5, U7.11 (B8)
U8_B1: U8.18 (B1)
U8_B2: U8.17 (B2)
U8_B3: J7.6, U8.16 (B3)
U8_B4: J7.4, U8.15 (B4)
U8_B5: J7.2, U8.14 (B5)
U8_B6: J7.1, U8.13 (B6)
U8_B7: J7.3, U8.12 (B7)
U8_B8: J7.5, U8.11 (B8)
U9_A1: C23.2, R26.1, R31.1, U9.3 (A1)
U9_A2: C24.2, R32.1, R33.1, U9.4 (A2)
U9_A3: C25.2, R34.1, R35.1, U9.5 (A3)
U9_A4: C26.2, R36.1, R37.1, U9.6 (A4)
U9_A5: U9.7 (A5)
U9_A6: U9.8 (A6)
U9_A7: U9.9 (A7)
U9_A8: U9.10 (A8)
U9_B1: U9.21 (B1)
U9_B3: U9.20 (B3)
U9_B3_2: U9.19 (B3_2)
U9_B4: U9.18 (B4)
U9_B5: U9.17 (B5)
U9_B6: U9.16 (B6)
U9_B7: U9.15 (B7)
U9_B8: U9.14 (B8)
U11_R1IN: R46.1, U11.13 (R1IN)
U11_R1OUT: IC5.7 (VIA), U11.12 (R1OUT)
U11_R2IN: R61.1, U11.8 (R2IN)
U11_R2OUT: IC6.7 (VIA), U11.9 (R2OUT)
U11_T1IN: IC5.6 (VOB), U11.11 (T1IN)
U11_T1OUT: R60.1, U11.14 (T1OUT)
U11_T2IN: IC6.6 (VOB), U11.10 (T2IN)
U11_T2OUT: R63.1, U11.7 (T2OUT)
U14_1Y: R52.1, R53.1, U14.6 (1Y)
U14_2Y: R57.1, R58.1, U14.4 (2Y)
VC: C39.1, IC5.8 (VDD2), IC6.8 (VDD2), J10.4, J11.4, U11.16 (VCC)
XYZ_EN: D14.2, J7.7, J7.8, U22.3 (C)
Z+_EDX: J13.7, U10.14 (4Y)
Z+_EXB: J14.7, U5.2 (1Y)
Z-_EDX: J13.8, U10.15 (4A)
Z-_EXB: J14.8, U5.1 (1A)

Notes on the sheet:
12v and 3.3v isolated power supply

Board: 2 copper layers, 186 parts (0 on the bottom side), 205 nets, no tracks yet.

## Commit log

2019-12-31 Initial Commit of PCB
    Still need to add routes and confirm correct pinout.
2019-12-31 3D Image
    This is a 3D image of the board in fusion 360.
2019-12-31 Updated Read Me
2019-12-31 Backlink to CADLAB.io has been added.

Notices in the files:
parts and their libraries:
LED: Licensing: Creative Commons ShareAlike 4.0 International - https://creativecommons.org/licenses/by-sa/4.0
COPYRIGHT: Copyright (C) 2018 Accelerated Designs. All rights reserved
